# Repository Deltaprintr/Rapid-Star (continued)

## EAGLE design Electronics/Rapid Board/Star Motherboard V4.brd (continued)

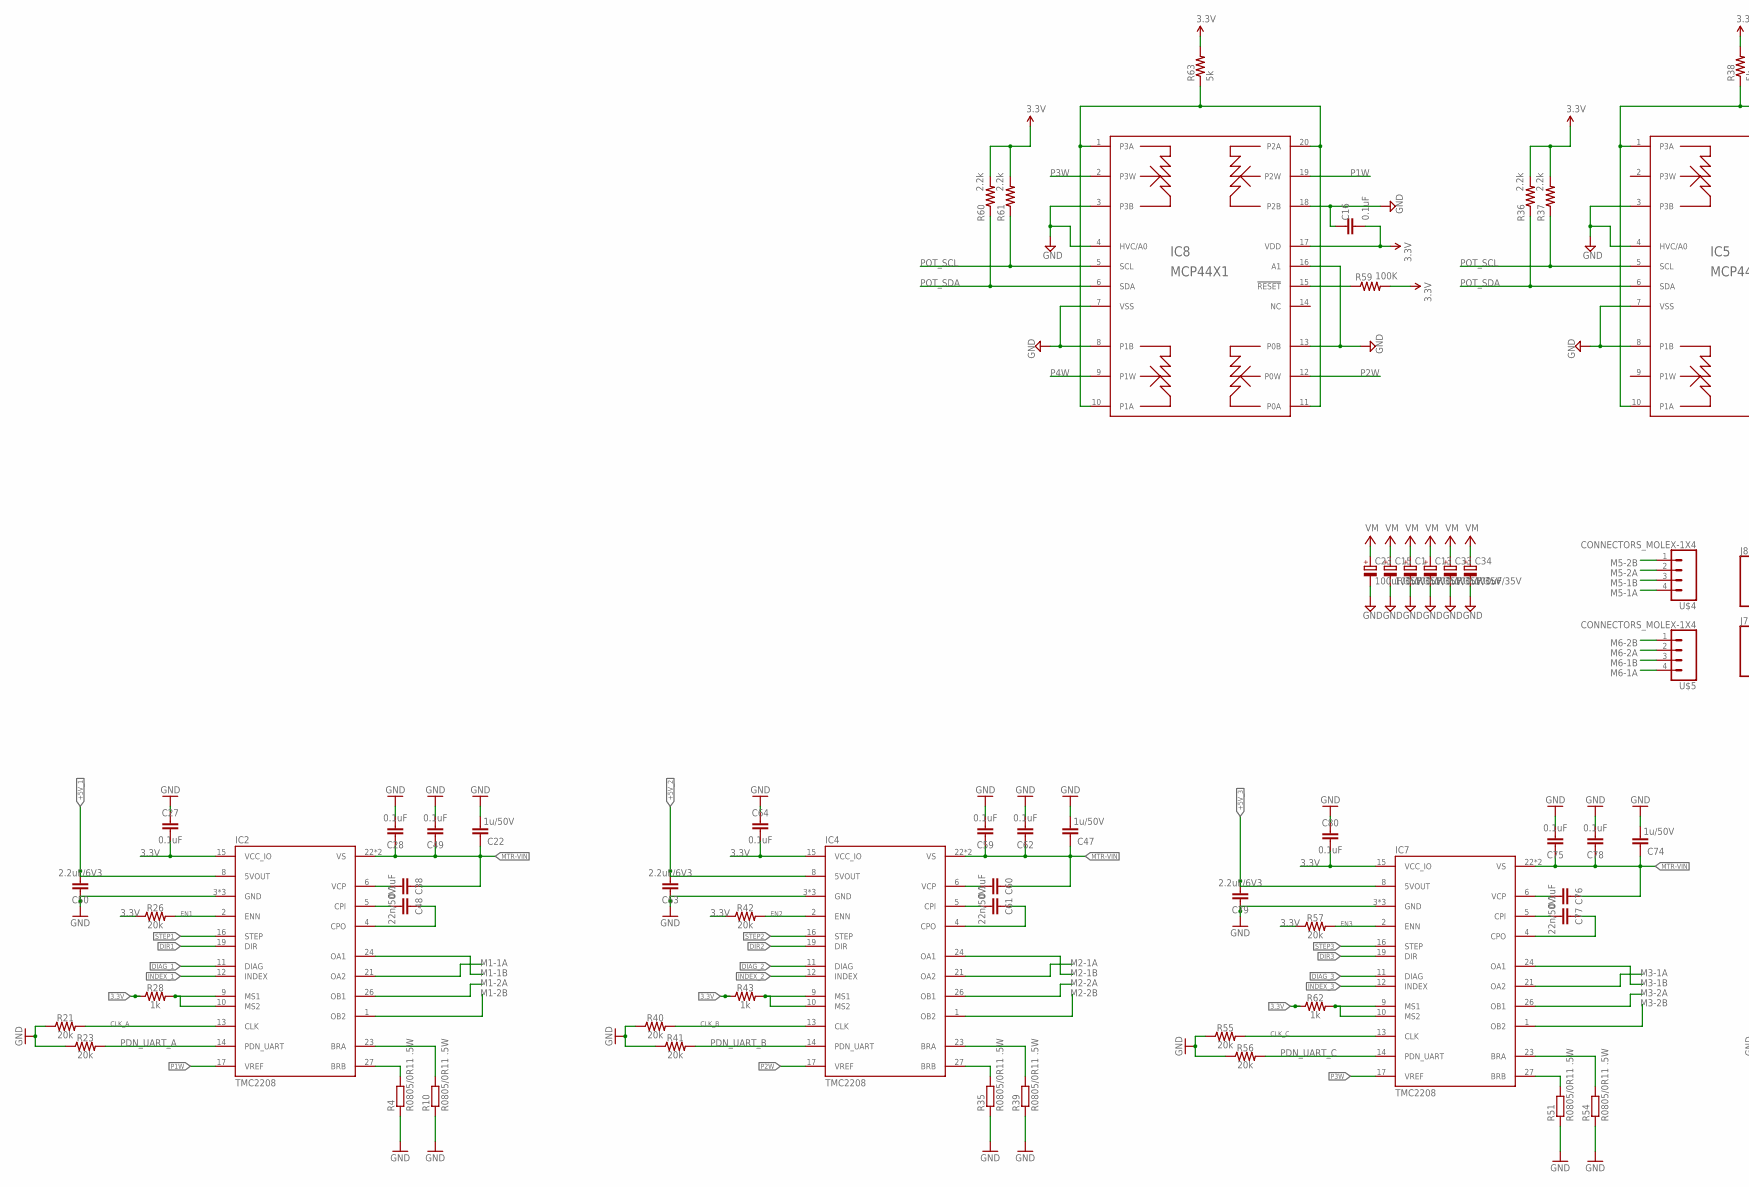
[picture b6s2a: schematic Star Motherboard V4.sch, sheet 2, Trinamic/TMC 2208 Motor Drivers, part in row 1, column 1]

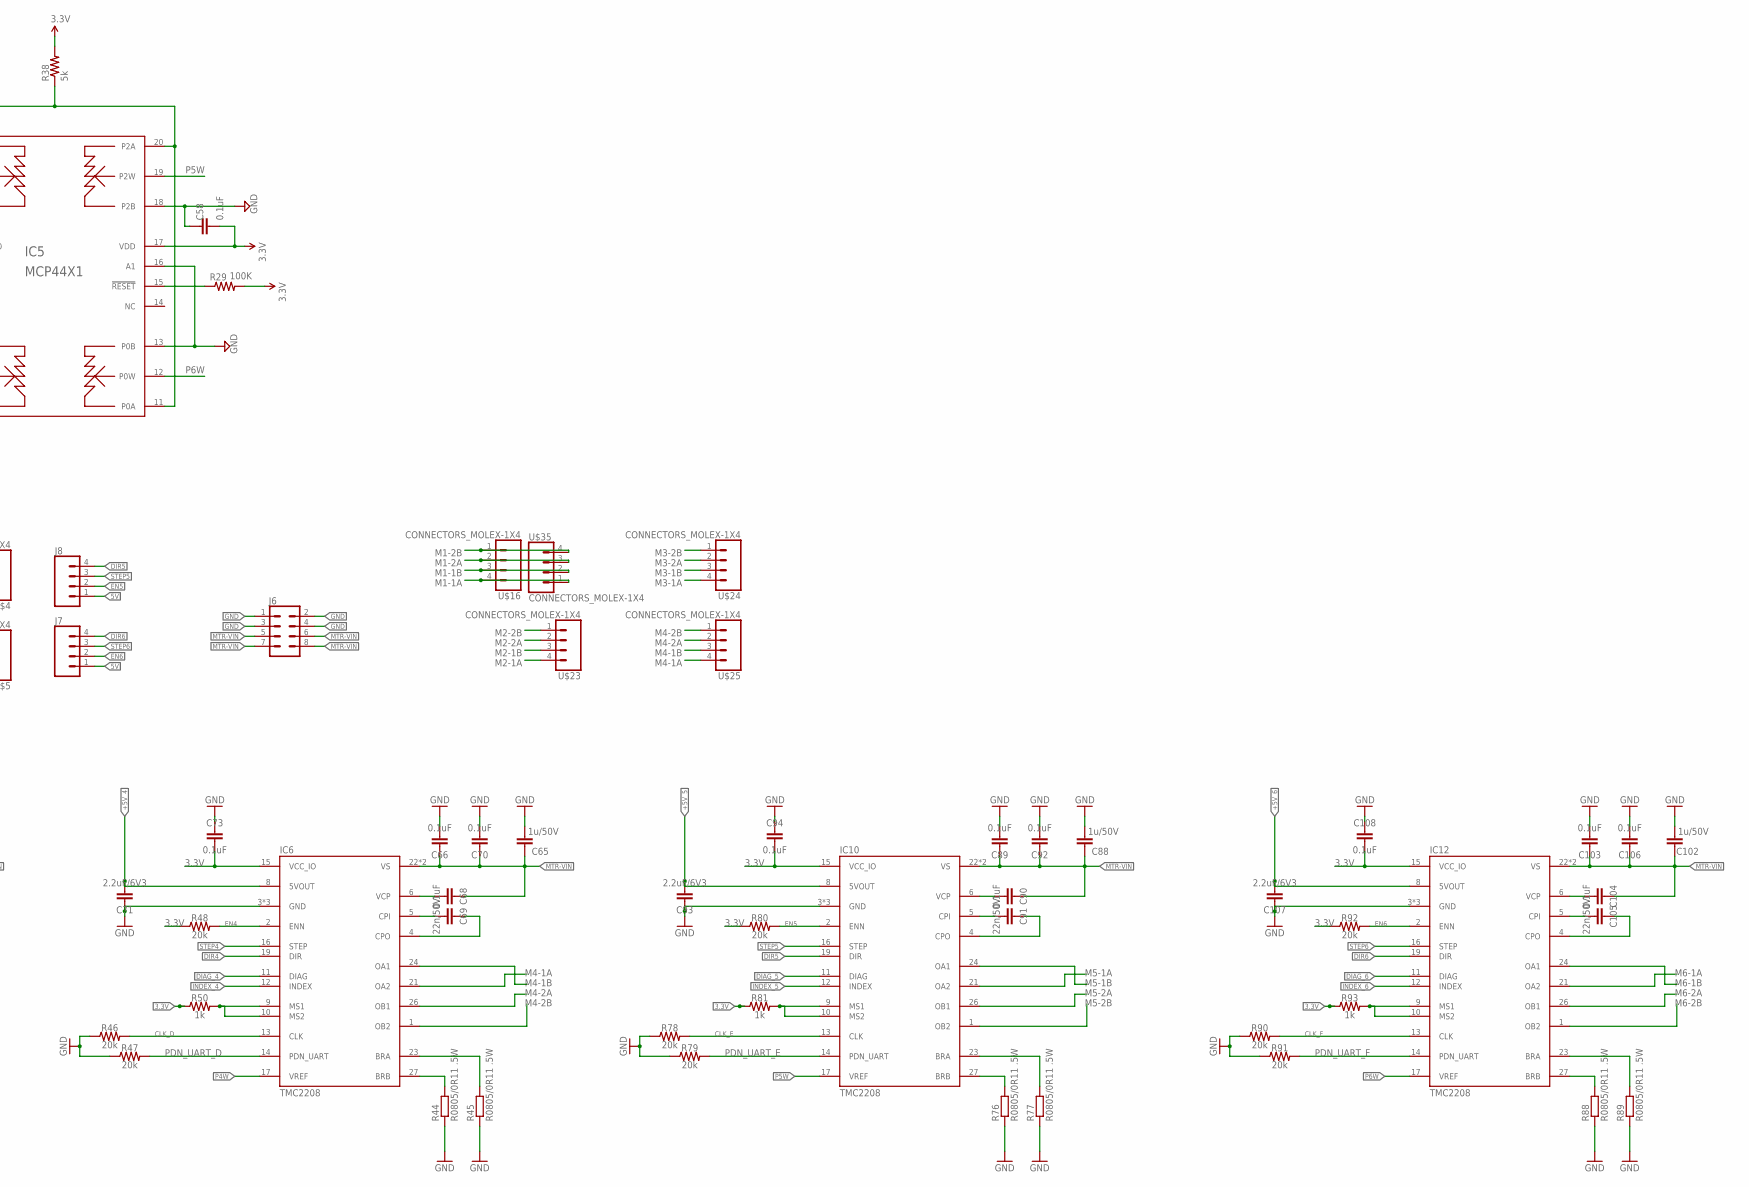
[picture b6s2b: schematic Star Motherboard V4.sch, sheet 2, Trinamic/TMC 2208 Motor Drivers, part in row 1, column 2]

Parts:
C1, C13, C15, C23, C33, C34: 100uF/35V; 153CLV-0605
C16, C27, C28, C38, C49, C58, C59, C60, C62, C64, C66, C68, C70, C73, C75, C76, C78, C80, C89, C90, C92, C94, C103, C104, C106, C108: 0.1uF; CAP_0603
C22, C47, C65, C74, C88, C102: 1u/50V; C0805
C48, C61, C69, C77, C91, C105: 22n/50V; CAP_0603
C50, C63, C71, C79, C93, C107: 2.2uF/6V3; CAP_0603
IC2, IC4, IC6, IC7, IC10, IC12: TMC2208; QFN28-PAD
IC5, IC8: MCP44X1; TSSOP20
J6: CONN_04X2; 2X4
J7, J8: CONN_04; 1X04
R4, R10, R35, R39, R44, R45, R51, R54, R76, R77, R88, R89: R0805/0R11 .5W; R0805
R21, R23, R26, R40, R41, R42, R46, R47, R48, R55, R56, R57, R78, R79, R80, R90, R91, R92: 20k; RESISTOR_0603
R28, R43, R50, R62, R81, R93: 1k; RESISTOR_0603
R29, R59: 100K; RESISTOR_0603
R36, R37, R60, R61: 2.2k; RESISTOR_0603
R38, R63: 5k; RESISTOR_0603
U$4, U$5, U$16, U$23, U$24, U$25, U$35: CONNECTORS_MOLEX-1X4

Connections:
3.3V: C16.2, C27.2, C58.2, C64.2, C73.2, C80.2, C94.2, C108.2, IC2.15 (VCC_IO), IC4.15 (VCC_IO), IC5.17 (VDD), IC6.15 (VCC_IO), IC7.15 (VCC_IO), IC8.17 (VDD), IC10.15 (VCC_IO), IC12.15 (VCC_IO), R26.1, R28.1, R29.2, R36.2, R37.2, R38.2, R42.1, R43.1, R48.1, R50.1, R57.1, R59.2, R60.2, R61.2, R62.1, R63.2, R80.1, R81.1, R92.1, R93.1; also elsewhere on the board
5V: J7.1, J8.1; also elsewhere on the board
+5V_1: C50.2, IC2.8 (5VOUT)
+5V_2: C63.2, IC4.8 (5VOUT)
+5V_3: C79.2, IC7.8 (5VOUT)
+5V_4: C71.2, IC6.8 (5VOUT)
+5V_5: C93.2, IC10.8 (5VOUT)
+5V_6: C107.2, IC12.8 (5VOUT)
BRA2: IC2.23 (BRA), R10.2
BRA3: IC4.23 (BRA), R39.2
BRA4: IC6.23 (BRA), R45.2
BRA5: IC7.23 (BRA), R54.2
BRA7: IC10.23 (BRA), R77.2
BRA9: IC12.23 (BRA), R89.2
BRB2: IC2.27 (BRB), R4.2
BRB3: IC4.27 (BRB), R35.2
BRB4: IC6.27 (BRB), R44.2
BRB5: IC7.27 (BRB), R51.2
BRB7: IC10.27 (BRB), R76.2
BRB9: IC12.27 (BRB), R88.2
CLK_A: IC2.13 (CLK), R21.2
CLK_B: IC4.13 (CLK), R40.2
CLK_C: IC7.13 (CLK), R55.2
CLK_D: IC6.13 (CLK), R46.2
CLK_E: IC10.13 (CLK), R78.2
CLK_F: IC12.13 (CLK), R90.2
CPI2: C48.2, IC2.5 (CPI)
CPI3: C61.2, IC4.5 (CPI)
CPI4: C69.2, IC6.5 (CPI)
CPI6: C77.2, IC7.5 (CPI)
CPI8: C91.2, IC10.5 (CPI)
CPI10: C105.2, IC12.5 (CPI)
CPO2: C48.1, IC2.4 (CPO)
CPO3: C61.1, IC4.4 (CPO)
CPO4: C69.1, IC6.4 (CPO)
CPO6: C77.1, IC7.4 (CPO)
CPO8: C91.1, IC10.4 (CPO)
CPO10: C105.1, IC12.4 (CPO)
DIAG_1: IC2.11 (DIAG)
DIAG_2: IC4.11 (DIAG)
DIAG_3: IC7.11 (DIAG)
DIAG_4: IC6.11 (DIAG)
DIAG_5: IC10.11 (DIAG)
DIAG_6: IC12.11 (DIAG)
DIR1: IC2.19 (DIR); also elsewhere on the board
DIR2: IC4.19 (DIR); also elsewhere on the board
DIR3: IC7.19 (DIR); also elsewhere on the board
DIR4: IC6.19 (DIR); also elsewhere on the board
DIR5: IC10.19 (DIR), J8.4; also elsewhere on the board
DIR6: IC12.19 (DIR), J7.4; also elsewhere on the board
EN1: IC2.2 (ENN), R26.2; also elsewhere on the board
EN2: IC4.2 (ENN), R42.2; also elsewhere on the board
EN3: IC7.2 (ENN), R57.2; also elsewhere on the board
EN4: IC6.2 (ENN), R48.2; also elsewhere on the board
EN5: IC10.2 (ENN), J8.2, R80.2; also elsewhere on the board
EN6: IC12.2 (ENN), J7.2, R92.2; also elsewhere on the board
GND: C1.-, C13.-, C15.-, C16.1, C22.2, C23.-, C27.1, C28.2, C33.-, C34.-, C47.2, C49.2, C50.1, C58.1, C59.2, C62.2, C63.1, C64.1, C65.2, C66.2, C70.2, C71.1, C73.1, C74.2, C75.2, C78.2, C79.1, C80.1, C88.2, C89.2, C92.2, C93.1, C94.1, C102.2, C103.2, C106.2, C107.1, C108.1, IC2.3 (GND), IC2.18 (GND), IC2.TP (GND), IC4.3 (GND), IC4.18 (GND), IC4.TP (GND), IC5.3 (P3B), IC5.4 (HVC/A0), IC5.7 (VSS), IC5.8 (P1B), IC5.13 (P0B), IC5.16 (A1), IC5.18 (P2B), IC6.3 (GND), IC6.18 (GND), IC6.TP (GND), IC7.3 (GND), IC7.18 (GND), IC7.TP (GND), IC8.3 (P3B), IC8.4 (HVC/A0), IC8.7 (VSS), IC8.8 (P1B), IC8.13 (P0B), IC8.16 (A1), IC8.18 (P2B), IC10.3 (GND), IC10.18 (GND), IC10.TP (GND), IC12.3 (GND), IC12.18 (GND), IC12.TP (GND), J6.1, J6.2, J6.3, J6.4, R4.1, R10.1, R21.1, R23.1, R35.1, R39.1, R40.1, R41.1, R44.1, R45.1, R46.1, R47.1, R51.1, R54.1, R55.1, R56.1, R76.1, R77.1, R78.1, R79.1, R88.1, R89.1, R90.1, R91.1; also elsewhere on the board
INDEX_1: IC2.12 (INDEX)
INDEX_2: IC4.12 (INDEX)
INDEX_3: IC7.12 (INDEX)
INDEX_4: IC6.12 (INDEX)
INDEX_5: IC10.12 (INDEX)
INDEX_6: IC12.12 (INDEX)
M1-1A: IC2.21 (OA2), U$16.4, U$35.1
M1-1B: IC2.24 (OA1), U$16.3, U$35.2
M1-2A: IC2.26 (OB1), U$16.2, U$35.3
M1-2B: IC2.1 (OB2), U$16.1, U$35.4
M2-1A: IC4.21 (OA2), U$23.4
M2-1B: IC4.24 (OA1), U$23.3
M2-2A: IC4.26 (OB1), U$23.2
M2-2B: IC4.1 (OB2), U$23.1
M3-1A: IC7.21 (OA2), U$24.4
M3-1B: IC7.24 (OA1), U$24.3
M3-2A: IC7.26 (OB1), U$24.2
M3-2B: IC7.1 (OB2), U$24.1
M4-1A: IC6.21 (OA2), U$25.4
M4-1B: IC6.24 (OA1), U$25.3
M4-2A: IC6.26 (OB1), U$25.2
M4-2B: IC6.1 (OB2), U$25.1
M5-1A: IC10.21 (OA2), U$4.4
M5-1B: IC10.24 (OA1), U$4.3
M5-2A: IC10.26 (OB1), U$4.2
M5-2B: IC10.1 (OB2), U$4.1
M6-1A: IC12.21 (OA2), U$5.4
M6-1B: IC12.24 (OA1), U$5.3
M6-2A: IC12.26 (OB1), U$5.2
M6-2B: IC12.1 (OB2), U$5.1
MSX2: IC2.9 (MS1), IC2.10 (MS2), R28.2
MSX3: IC4.9 (MS1), IC4.10 (MS2), R43.2
MSX4: IC6.9 (MS1), IC6.10 (MS2), R50.2
MSX5: IC7.9 (MS1), IC7.10 (MS2), R62.2
MSX7: IC10.9 (MS1), IC10.10 (MS2), R81.2
MSX9: IC12.9 (MS1), IC12.10 (MS2), R93.2
MTR-VIN: C1.+, C13.+, C15.+, C22.1, C23.+, C28.1, C33.+, C34.+, C38.1, C47.1, C49.1, C59.1, C60.1, C62.1, C65.1, C66.1, C68.1, C70.1, C74.1, C75.1, C76.1, C78.1, C88.1, C89.1, C90.1, C92.1, C102.1, C103.1, C104.1, C106.1, IC2.22 (VS), IC2.28 (VS), IC4.22 (VS), IC4.28 (VS), IC6.22 (VS), IC6.28 (VS), IC7.22 (VS), IC7.28 (VS), IC10.22 (VS), IC10.28 (VS), IC12.22 (VS), IC12.28 (VS), J6.5, J6.6, J6.7, J6.8; also elsewhere on the board
unnamed: IC8.15 (!RESET), R59.1
unnamed: IC8.1 (P3A), IC8.10 (P1A), IC8.11 (P0A), IC8.20 (P2A), R63.1
unnamed: IC5.15 (!RESET), R29.1
unnamed: IC5.1 (P3A), IC5.10 (P1A), IC5.11 (P0A), IC5.20 (P2A), R38.1
P1W: IC2.17 (VREF), IC8.19 (P2W)
P2W: IC4.17 (VREF), IC8.12 (P0W)
P3W: IC7.17 (VREF), IC8.2 (P3W)
P4W: IC6.17 (VREF), IC8.9 (P1W)
P5W: IC5.19 (P2W), IC10.17 (VREF)
P6W: IC5.12 (P0W), IC12.17 (VREF)
PDN_UART_A: IC2.14 (PDN_UART), R23.2
PDN_UART_B: IC4.14 (PDN_UART), R41.2
PDN_UART_C: IC7.14 (PDN_UART), R56.2
PDN_UART_D: IC6.14 (PDN_UART), R47.2
PDN_UART_E: IC10.14 (PDN_UART), R79.2
PDN_UART_F: IC12.14 (PDN_UART), R91.2
POT_SCL: IC5.5 (SCL), IC8.5 (SCL), R37.1, R61.1; also elsewhere on the board
POT_SDA: IC5.6 (SDA), IC8.6 (SDA), R36.1, R60.1; also elsewhere on the board
STEP1: IC2.16 (STEP); also elsewhere on the board
STEP2: IC4.16 (STEP); also elsewhere on the board
STEP3: IC7.16 (STEP); also elsewhere on the board
STEP4: IC6.16 (STEP); also elsewhere on the board
STEP5: IC10.16 (STEP), J8.3; also elsewhere on the board
STEP6: IC12.16 (STEP), J7.3; also elsewhere on the board
VCP2: C38.2, IC2.6 (VCP)
VCP3: C60.2, IC4.6 (VCP)
VCP4: C68.2, IC6.6 (VCP)
VCP6: C76.2, IC7.6 (VCP)
VCP8: C90.2, IC10.6 (VCP)
VCP10: C104.2, IC12.6 (VCP)

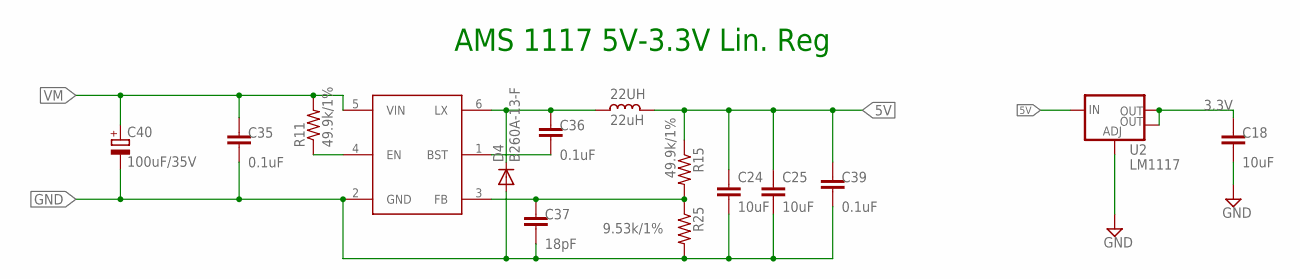
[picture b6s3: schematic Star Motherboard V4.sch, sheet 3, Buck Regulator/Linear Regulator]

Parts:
22UH: 22uH; CD75
C18: 10uF; CAP_0603
C24, C25: 10uF; C0805
C35, C36, C39: 0.1uF; CAP_0603
C37: 18pF; CAP_0603
C40: 100uF/35V; 153CLV-0605
D4: B260A-13-F; DO-214AC
R11, R15: 49.9k/1%; RESISTOR_0603
R25: 9.53k/1%; RESISTOR_0603
U2: LM1117; SOT223
U$2: AOZ1282CI; SOT23-6

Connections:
3.3V: C18.1, U2.2 (OUT), U2.4 (OUT); also elsewhere on the board
5V: 22UH.1, C24.1, C25.1, C39.1, R15.1, U2.3 (IN); also elsewhere on the board
GND: C18.2, C24.2, C25.2, C35.2, C37.2, C39.2, C40.-, D4.2 (A), R25.2, U2.1 (ADJ), U$2.2 (GND); also elsewhere on the board
unnamed: R11.1, U$2.4 (EN)
unnamed: C36.2, U$2.1 (BST)
unnamed: 22UH.2, C36.1, D4.1 (C), U$2.6 (LX)
unnamed: C37.1, R15.2, R25.1, U$2.3 (FB)
VM: C35.1, C40.+, R11.2, U$2.5 (VIN); also elsewhere on the board

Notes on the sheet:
AMS 1117 5V-3.3V Lin. Reg

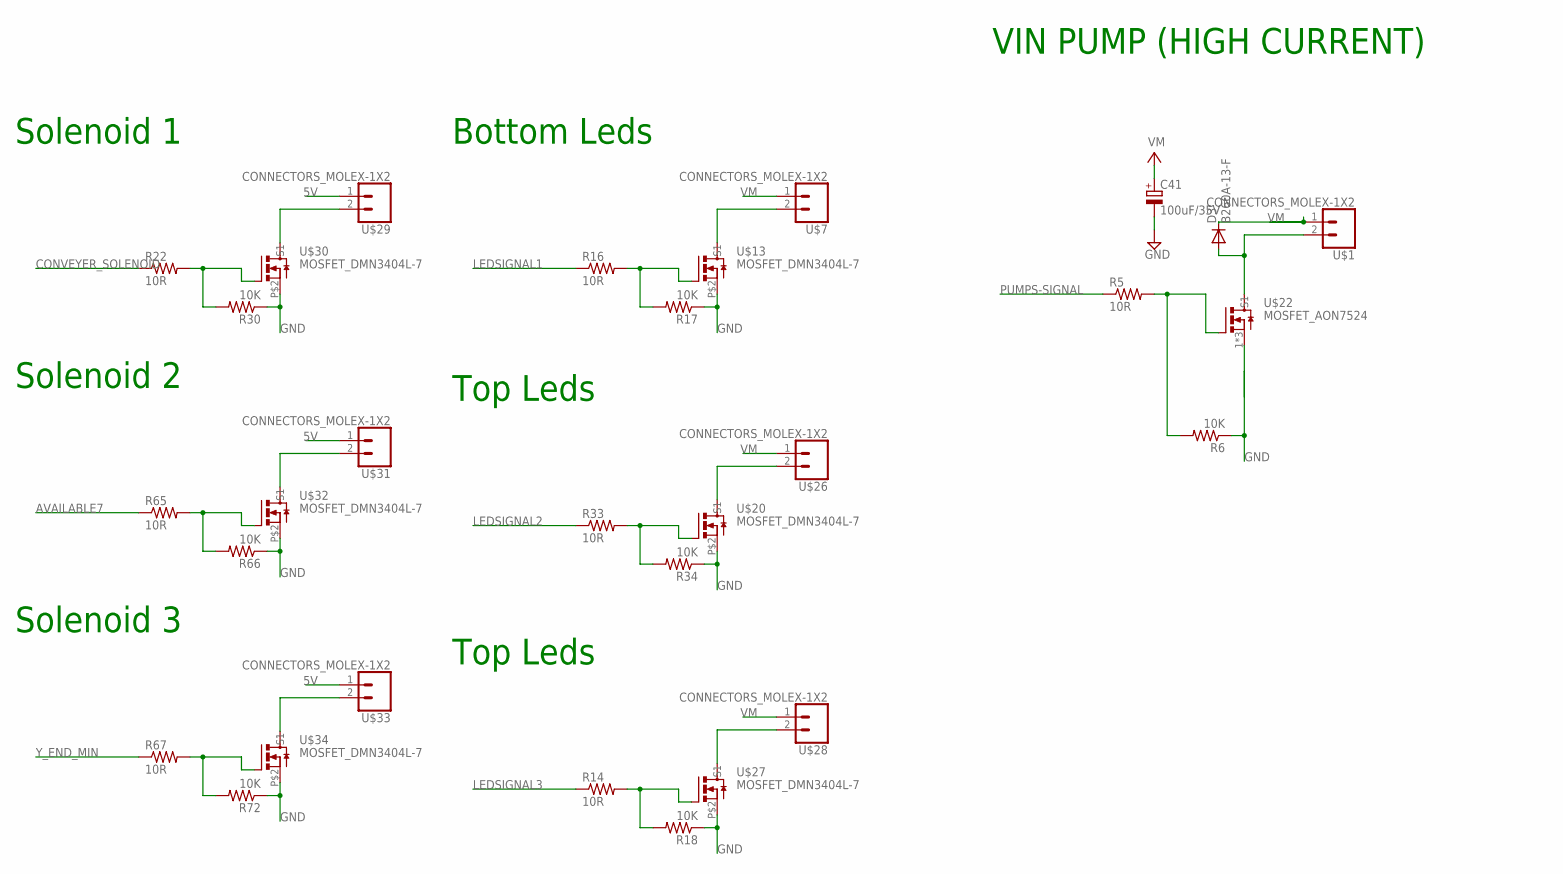
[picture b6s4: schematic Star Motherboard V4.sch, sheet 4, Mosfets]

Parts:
C41: 100uF/35V; 153CLV-0605
D3: B260A-13-F; DO-214AC
R5, R14, R16, R22, R33, R65, R67: 10R; RESISTOR_0603
R6, R17, R18, R30, R34, R66, R72: 10K; RESISTOR_0603
U$1, U$7, U$26, U$28, U$29, U$31, U$33: CONNECTORS_MOLEX-1X2
U$13, U$20, U$27, U$30, U$32, U$34: MOSFET_DMN3404L-7
U$22: MOSFET_AON7524

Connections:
5V: U$29.1, U$31.1, U$33.1; also elsewhere on the board
AVAILABLE7: R65.1; also elsewhere on the board
CONVEYER_SOLENOID: R22.1; also elsewhere on the board
GND: C41.-, R6.1, R17.1, R18.1, R30.1, R34.1, R66.1, R72.1, U$13.P$2 (S1), U$20.P$2 (S1), U$22.1 (S1), U$22.2 (S1), U$22.3 (S1), U$27.P$2 (S1), U$30.P$2 (S1), U$32.P$2 (S1), U$34.P$2 (S1); also elsewhere on the board
LEDSIGNAL1: R16.1; also elsewhere on the board
LEDSIGNAL2: R33.1; also elsewhere on the board
LEDSIGNAL3: R14.1; also elsewhere on the board
unnamed: R16.2, R17.2, U$13.P$3 (G1)
unnamed: R33.2, R34.2, U$20.P$3 (G1)
unnamed: R5.2, R6.2, U$22.4 (G1)
unnamed: R14.2, R18.2, U$27.P$3 (G1)
unnamed: R22.2, R30.2, U$30.P$3 (G1)
unnamed: R65.2, R66.2, U$32.P$3 (G1)
unnamed: R67.2, R72.2, U$34.P$3 (G1)
PUMPS-SIGNAL: R5.1; also elsewhere on the board
TOP-LED-POWER: U$20.P$1 (D1), U$26.2
TOP-LED-POWER1: U$27.P$1 (D1), U$28.2
VIBRATOR_FET_CONTROL1: U$7.2, U$13.P$1 (D1)
VIBRATOR_FET_CONTROL2: D3.2 (A), U$1.2, U$22.5 (D1), U$22.6 (D1), U$22.7 (D1), U$22.8 (D1), U$22.9 (D1), U$22.10 (D1), U$22.11 (D1)
VIBRATOR_FET_CONTROL3: U$29.2, U$30.P$1 (D1)
VIBRATOR_FET_CONTROL4: U$31.2, U$32.P$1 (D1)
VIBRATOR_FET_CONTROL5: U$33.2, U$34.P$1 (D1)
VM: C41.+, D3.1 (C), U$1.1, U$7.1, U$26.1, U$28.1; also elsewhere on the board
Y_END_MIN: R67.1; also elsewhere on the board

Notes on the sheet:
Bottom Leds
Top Leds
VIN PUMP (HIGH CURRENT)
Solenoid 1
Solenoid 2
Solenoid 3

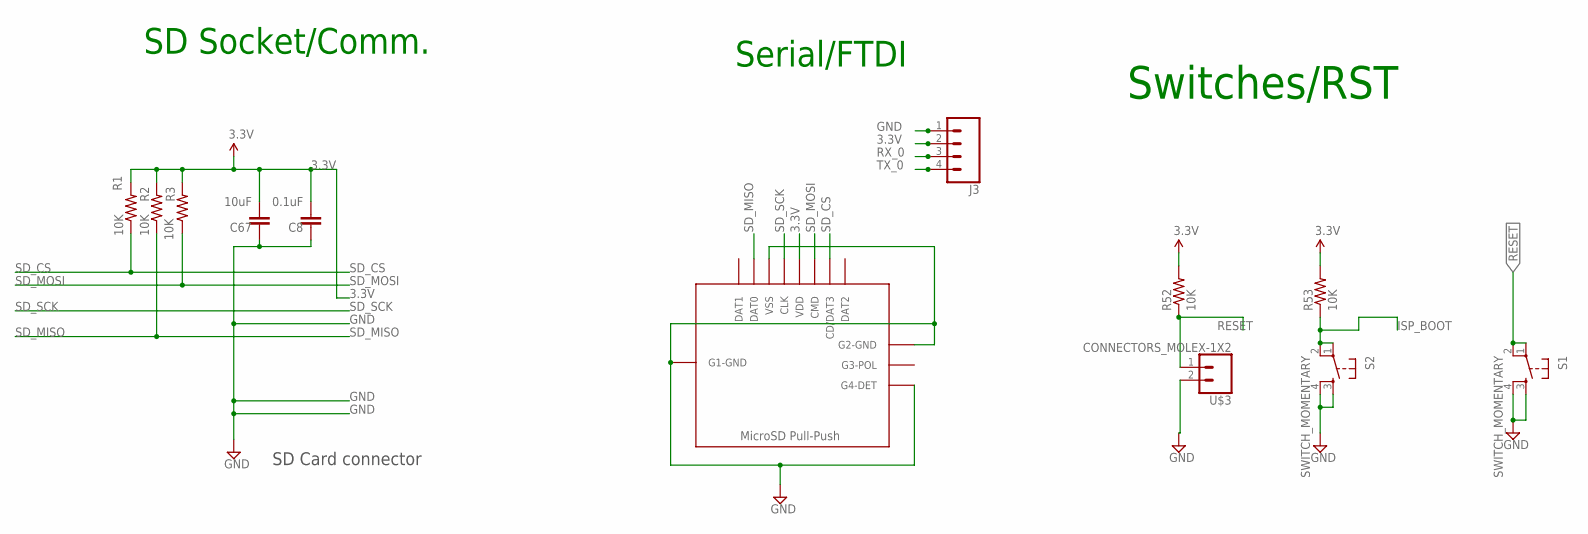
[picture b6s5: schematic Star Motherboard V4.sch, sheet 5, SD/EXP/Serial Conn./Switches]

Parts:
C8: 0.1uF; CAP_0603
C67: 10uF; CAP_0603
J3: CONN_04; 1X04
R1, R2, R3, R52, R53: 10K; RESISTOR_0603
S1, S2: SWITCH_MOMENTARY
U$3: CONNECTORS_MOLEX-1X2
U$12: MICROSD_PUSH-PULL

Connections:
3.3V: C8.2, C67.2, J3.2, R1.2, R2.2, R3.2, R52.2, R53.2, U$12.PIN4 (VDD); also elsewhere on the board
GND: C8.1, C67.1, J3.1, S1.3, S1.4, S2.3, S2.4, U$3.2, U$12.G1 (G1-GND), U$12.G2 (G2-GND), U$12.G4 (G4-DET), U$12.PIN6 (VSS); also elsewhere on the board
ISP_BOOT: R53.1, S2.1, S2.2; also elsewhere on the board
RESET: R52.1, S1.1, S1.2, U$3.1; also elsewhere on the board
RX_0: J3.3; also elsewhere on the board
SD_CS: R1.1, U$12.PIN2 (CD/DAT3); also elsewhere on the board
SD_MISO: R2.1, U$12.PIN7 (DAT0); also elsewhere on the board
SD_MOSI: R3.1, U$12.PIN3 (CMD); also elsewhere on the board
SD_SCK: U$12.PIN5 (CLK); also elsewhere on the board
TX_0: J3.4; also elsewhere on the board

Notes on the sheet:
SD Card connector
SD Socket/Comm.
Serial/FTDI
Switches/RST

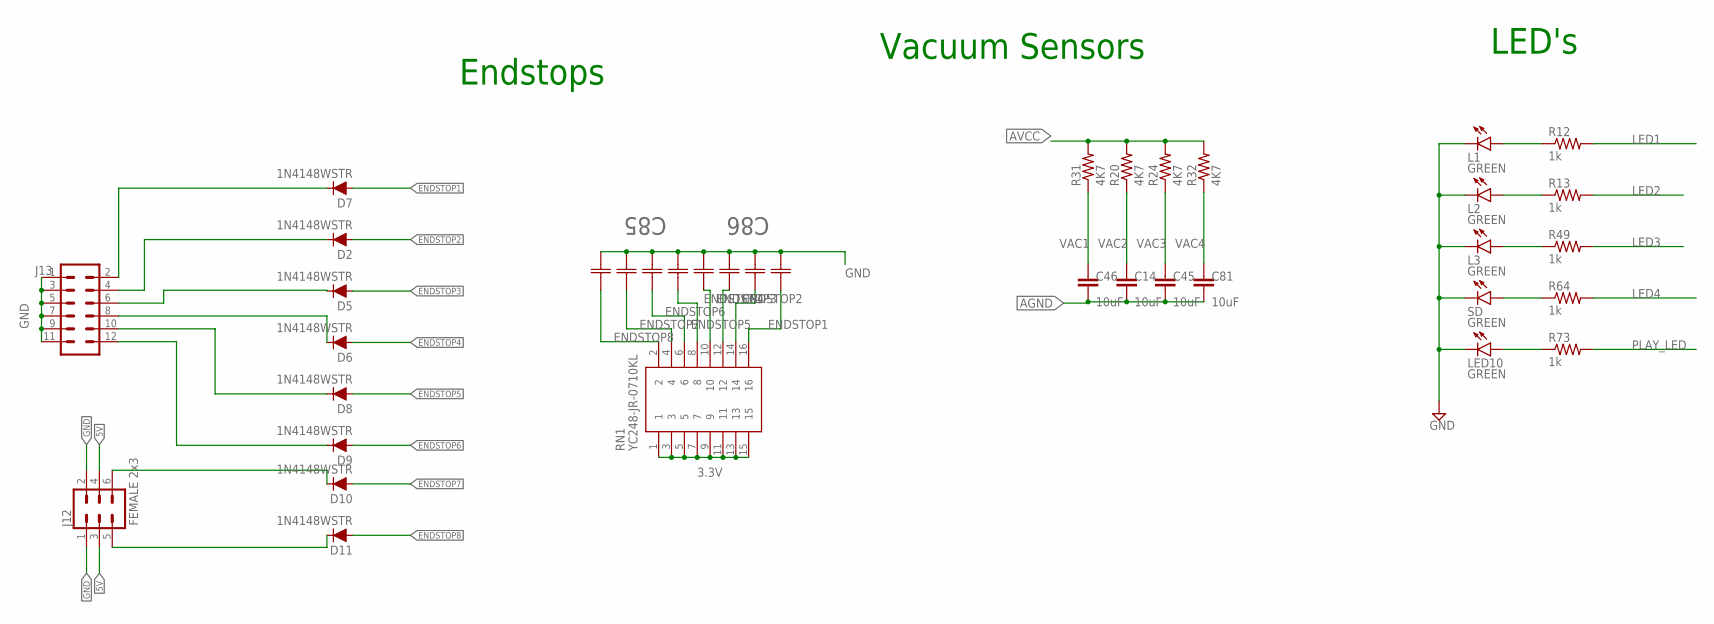
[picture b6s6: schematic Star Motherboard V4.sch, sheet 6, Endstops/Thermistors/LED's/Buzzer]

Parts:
C14, C45, C46, C81: 10uF; CAP_0603
C85, C86: CAP_ARRAY_CA064C104M4RAC7800; CA064_KEM
D2, D5, D6, D7, D8, D9, D10, D11: 1N4148WSTR; SOD-323
J12: FEMALE 2x3; 2X3
J13: 2X6 FEMALE; 2X6
L1, L2, L3: GREEN; LED-0603
LED10: GREEN; LED-0603
R12, R13, R49, R64, R73: 1k; RESISTOR_0603
R20, R24, R31, R32: 4K7; RESISTOR_0603
RN1: YC248-JR-0710KL; YC248JR0710KL
SD: GREEN; LED-0603

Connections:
3.3V: RN1.1, RN1.3, RN1.5, RN1.7, RN1.9, RN1.11, RN1.13, RN1.15; also elsewhere on the board
5V: J12.3, J12.4; also elsewhere on the board
AGND: C14.2, C45.2, C46.2, C81.2; also elsewhere on the board
AVCC: R20.2, R24.2, R31.2, R32.2; also elsewhere on the board
ENDSTOP1: C86.4, D7.A, RN1.16; also elsewhere on the board
ENDSTOP2: C86.3, D2.A, RN1.14; also elsewhere on the board
ENDSTOP3: C86.2, D5.A, RN1.12; also elsewhere on the board
ENDSTOP4: C86.1, D6.A, RN1.10; also elsewhere on the board
ENDSTOP5: C85.4, D8.A, RN1.8; also elsewhere on the board
ENDSTOP6: C85.3, D9.A, RN1.6; also elsewhere on the board
ENDSTOP7: C85.2, D10.A, RN1.4; also elsewhere on the board
ENDSTOP8: C85.1, D11.A, RN1.2; also elsewhere on the board
GND: C85.5, C85.6, C85.7, C85.8, C86.5, C86.6, C86.7, C86.8, J12.1, J12.2, J13.1, J13.3, J13.5, J13.7, J13.9, J13.11, L1.C, L2.C, L3.C, LED10.C, SD.C; also elsewhere on the board
LED1: R12.2; also elsewhere on the board
LED2: R13.2; also elsewhere on the board
LED3: R49.2; also elsewhere on the board
LED4: R64.2; also elsewhere on the board
unnamed: D7.C, J13.2
unnamed: D2.C, J13.4
unnamed: D5.C, J13.6
unnamed: D6.C, J13.8
unnamed: D8.C, J13.10
unnamed: LED10.A, R73.1
unnamed: D10.C, J12.6
unnamed: D11.C, J12.5
unnamed: D9.C, J13.12
unnamed: R64.1, SD.A
unnamed: L3.A, R49.1
unnamed: L2.A, R13.1
unnamed: L1.A, R12.1
PLAY_LED: R73.2; also elsewhere on the board
VAC1: C46.1, R31.1; also elsewhere on the board
VAC2: C14.1, R20.1; also elsewhere on the board
VAC3: C45.1, R24.1; also elsewhere on the board
VAC4: C81.1, R32.1; also elsewhere on the board

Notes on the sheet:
Endstops
LED's
Vacuum Sensors

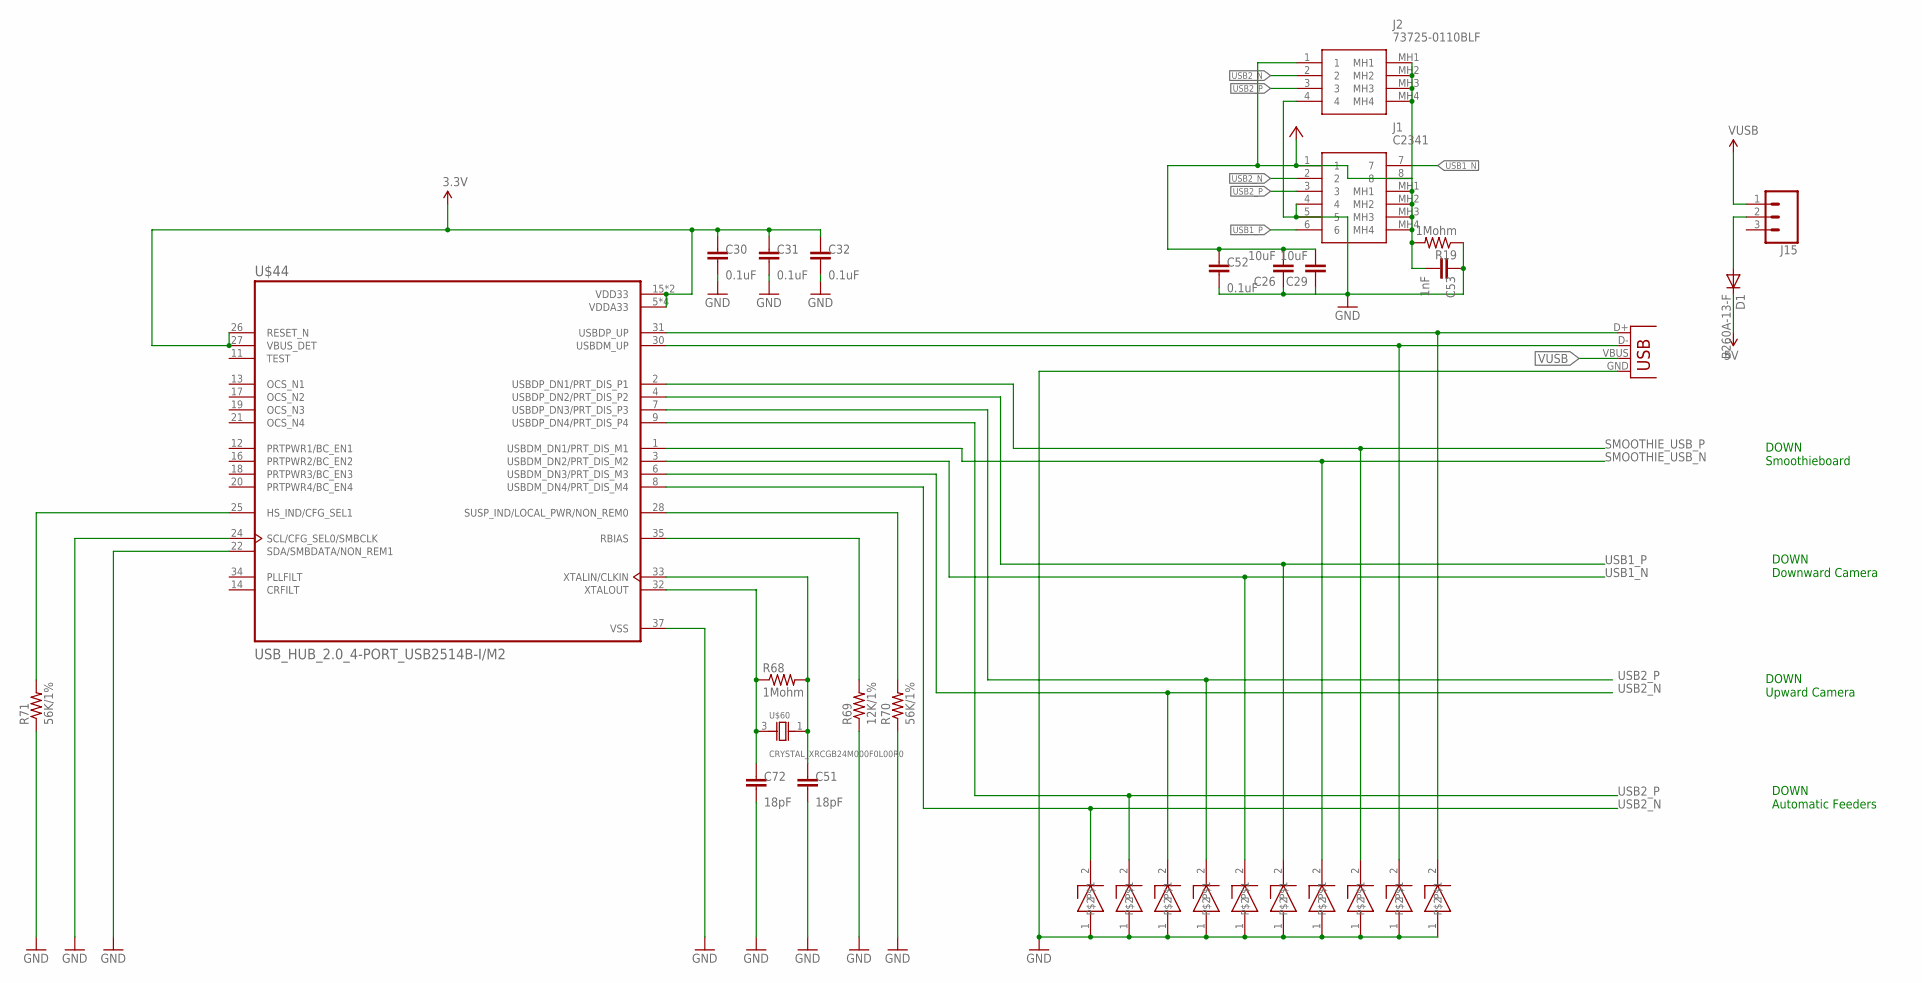
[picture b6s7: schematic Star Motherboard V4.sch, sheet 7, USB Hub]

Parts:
C26, C29: 10uF; C0805
C30, C31, C32, C52: 0.1uF; CAP_0603
C51, C72: 18pF; CAP_0603
C53: 1nF; CAP_0603
D1: B260A-13-F; DO-214AC
J1: C2341
J2: 73725-0110BLF; 737250110BLF
J15: CONN_03; 1X03
R19, R68: 1Mohm; RESISTOR_0603
R69: 12K/1%; RESISTOR_0603
R70, R71: 56K/1%; RESISTOR_0603
U$11: USB-B-PTH
U$14, U$15, U$18, U$19, U$50, U$51, U$56, U$57, U$58, U$59: DIODE_ESD_ESD9B3.3ST5G
U$44: USB_HUB_2.0_4-PORT_USB2514B-I/M2
U$60: CRYSTAL_XRCGB24M000F0L00R0

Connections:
3.3V: C30.1, C31.1, C32.1, U$44.5 (VDDA33), U$44.10 (VDDA33), U$44.15 (VDD33), U$44.23 (VDD33), U$44.26 (RESET_N), U$44.27 (VBUS_DET), U$44.29 (VDDA33), U$44.36 (VDDA33); also elsewhere on the board
5V: C26.2, C29.2, C52.1, D1.1 (C), J1.1, J1.8, J2.1; also elsewhere on the board
5VUSB: D1.2 (A), J15.2
D5_N: U$11.D-, U$44.30 (USBDM_UP), U$58.2
D5_P: U$11.D+, U$44.31 (USBDP_UP), U$59.2
GND: C26.1, C29.1, C30.2, C31.2, C32.2, C51.2, C52.2, C53.1, C72.2, J1.4, J1.5, J2.4, R19.1, R69.1, R70.1, R71.1, U$11.GND, U$14.1, U$15.1, U$18.1, U$19.1, U$44.22 (SDA/SMBDATA/NON_REM1), U$44.24 (SCL/CFG_SEL0/SMBCLK), U$44.37 (VSS), U$50.1, U$51.1, U$56.1, U$57.1, U$58.1, U$59.1; also elsewhere on the board
unnamed: C53.2, J1.MH1, J1.MH2, J1.MH3, J1.MH4, J2.MH1, J2.MH2, J2.MH3, J2.MH4, R19.2
unnamed: C51.1, R68.2, U$44.33 (XTALIN/CLKIN), U$60.1 (2)
unnamed: C72.1, R68.1, U$44.32 (XTALOUT), U$60.3 (1)
unnamed: R69.2, U$44.35 (RBIAS)
unnamed: R70.2, U$44.28 (SUSP_IND/LOCAL_PWR/NON_REM0)
unnamed: R71.2, U$44.25 (HS_IND/CFG_SEL1)
SMOOTHIE_USB_N: U$44.1 (USBDM_DN1/PRT_DIS_M1), U$56.2; also elsewhere on the board
SMOOTHIE_USB_P: U$44.2 (USBDP_DN1/PRT_DIS_P1), U$57.2; also elsewhere on the board
USB1_N: J1.7, U$18.2, U$44.3 (USBDM_DN2/PRT_DIS_M2)
USB1_P: J1.6, U$19.2, U$44.4 (USBDP_DN2/PRT_DIS_P2)
USB2_N: J1.2, J2.2, U$14.2, U$44.6 (USBDM_DN3/PRT_DIS_M3), U$44.8 (USBDM_DN4/PRT_DIS_M4), U$50.2
USB2_P: J1.3, J2.3, U$15.2, U$44.7 (USBDP_DN3/PRT_DIS_P3), U$44.9 (USBDP_DN4/PRT_DIS_P4), U$51.2
VUSB: J15.1, U$11.VBUS

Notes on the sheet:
DOWN Upward Camera
DOWN Downward Camera
DOWN Automatic Feeders
DOWN Smoothieboard

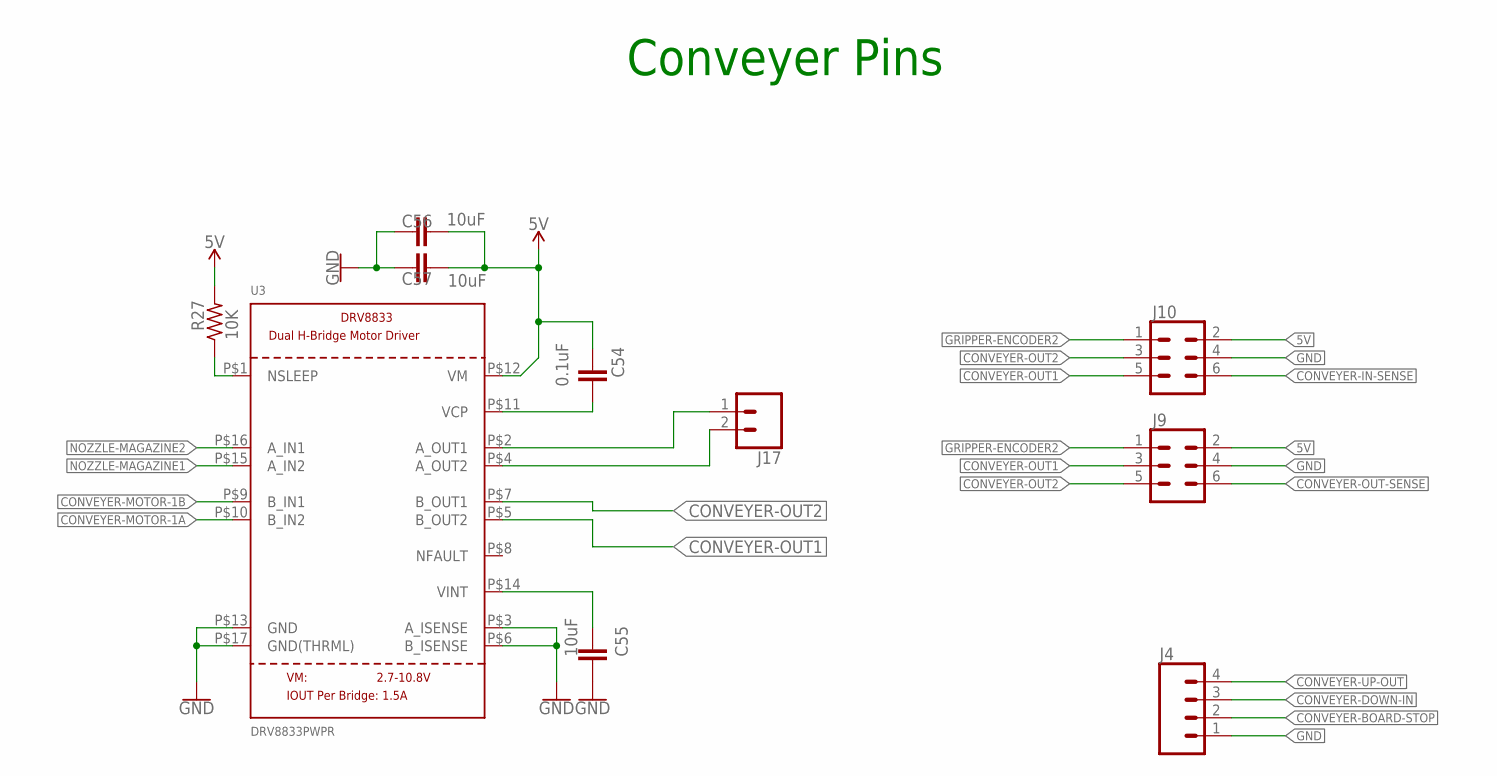
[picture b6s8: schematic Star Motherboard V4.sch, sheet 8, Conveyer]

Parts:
C54: 0.1uF; CAP_0603
C55, C56, C57: 10uF; C0805
J4: CONN_04; 1X04
J9, J10: CONN_03X22X3_SILK_MALE_PTH; 2X3
J17: CONN_02; 1X02
R27: 10K; RESISTOR_0603
U3: DRV8833PWPR; DRV8833

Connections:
5V: C54.1, C56.1, C57.1, J9.2, J10.2, R27.2, U3.P$12 (VM); also elsewhere on the board
!SLEEP: R27.1, U3.P$1 (NSLEEP)
CONVEYER-BOARD-STOP: J4.2; also elsewhere on the board
CONVEYER-DOWN-IN: J4.3; also elsewhere on the board
CONVEYER-IN-SENSE: J10.6; also elsewhere on the board
CONVEYER-MOTOR-1A: U3.P$10 (B_IN2); also elsewhere on the board
CONVEYER-MOTOR-1B: U3.P$9 (B_IN1); also elsewhere on the board
CONVEYER-OUT1: J9.3, J10.5, U3.P$5 (B_OUT2)
CONVEYER-OUT2: J9.5, J10.3, U3.P$7 (B_OUT1)
CONVEYER-OUT-SENSE: J9.6; also elsewhere on the board
CONVEYER-UP-OUT: J4.4; also elsewhere on the board
GND: C55.2, C56.2, C57.2, J4.1, J9.4, J10.4, U3.P$3 (A_ISENSE), U3.P$6 (B_ISENSE), U3.P$13 (GND), U3.P$17 (GND(THRML)); also elsewhere on the board
GRIPPER-ENCODER2: J9.1, J10.1; also elsewhere on the board
unnamed: C54.2, U3.P$11 (VCP)
unnamed: C55.1, U3.P$14 (VINT)
unnamed: J17.2, U3.P$4 (A_OUT2)
unnamed: J17.1, U3.P$2 (A_OUT1)
NOZZLE-MAGAZINE1: U3.P$15 (A_IN2); also elsewhere on the board
NOZZLE-MAGAZINE2: U3.P$16 (A_IN1)

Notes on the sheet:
Conveyer Pins

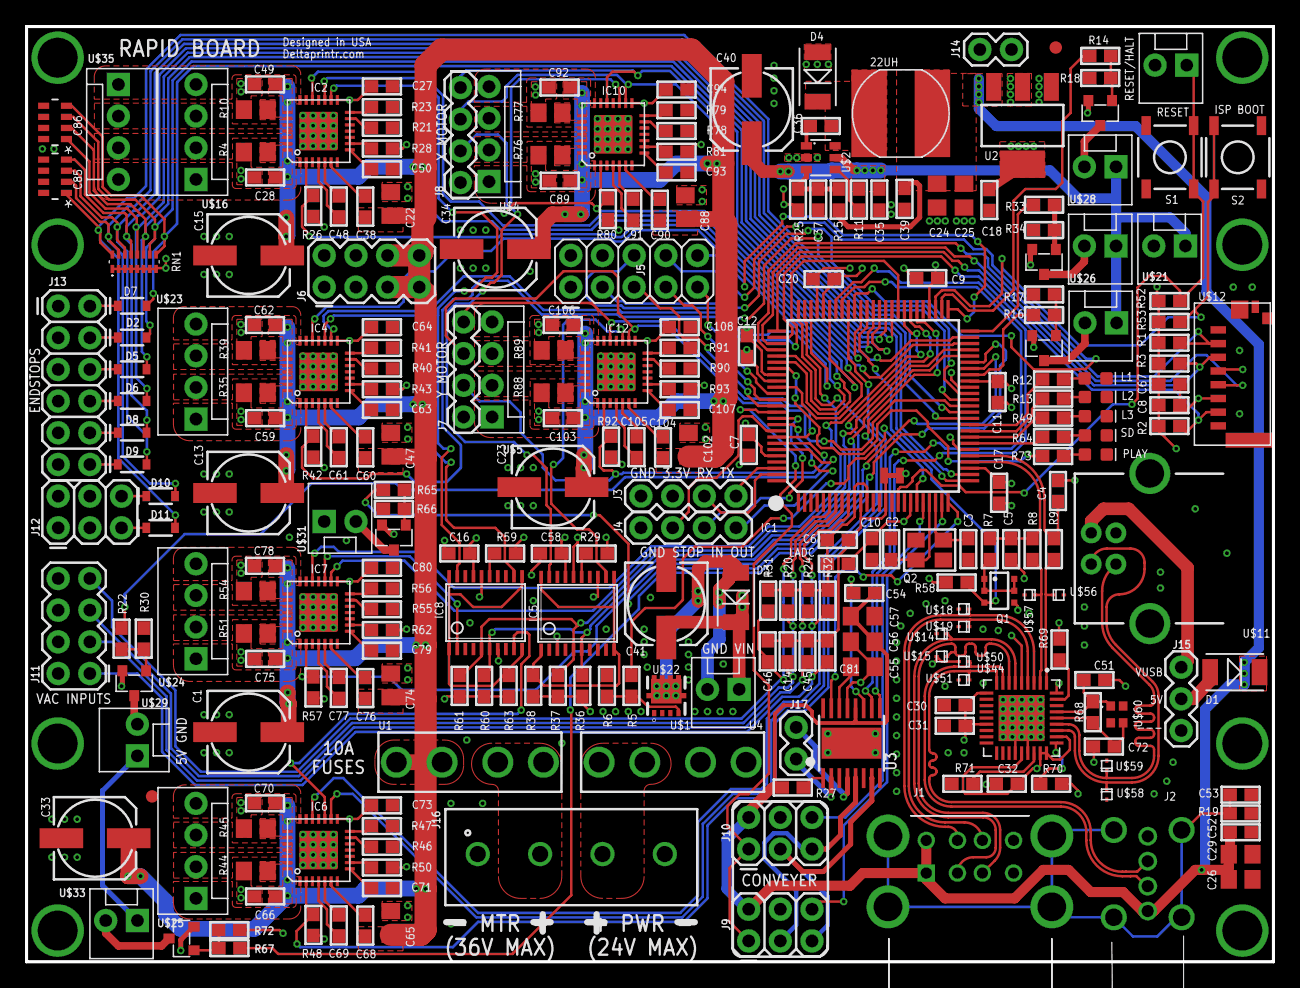
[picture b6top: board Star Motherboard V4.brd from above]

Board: 4 copper layers, 100.0 x 75.0 mm, 271 parts (0 on the bottom side), 225 nets.

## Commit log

2021-09-20 Added files
2021-09-20 Updated settings folder
2021-09-20 Electronics update
    Added feeder motherboard and extensions
2021-09-20 Updated files
2021-09-20 updated firmware file
2021-09-21 Added STEP file
2021-09-21 Updated folders
2021-09-21 Updated Mechanics
2021-09-21 Added IC Tray
2021-09-30 Updated settings
    Added support for nozzle angle offsets and updating MOVE_TO_COMMAND to include angles.
2021-10-01 Added lens calibration pcb
    PCB used to calibrate upward looking camera by running it through a gcode file that will maneuver it around the upward looking camera for lens distortion calibration.
2021-10-01 Upward Cam Gcode Path
    Added path for nozzle to take when doing lens calibration for upward camera.
2021-10-01 Updated extension
2021-10-02 Updated to include 5mm cube
2021-10-04 updated file name
2021-10-06 OpenPNP and Config updates
